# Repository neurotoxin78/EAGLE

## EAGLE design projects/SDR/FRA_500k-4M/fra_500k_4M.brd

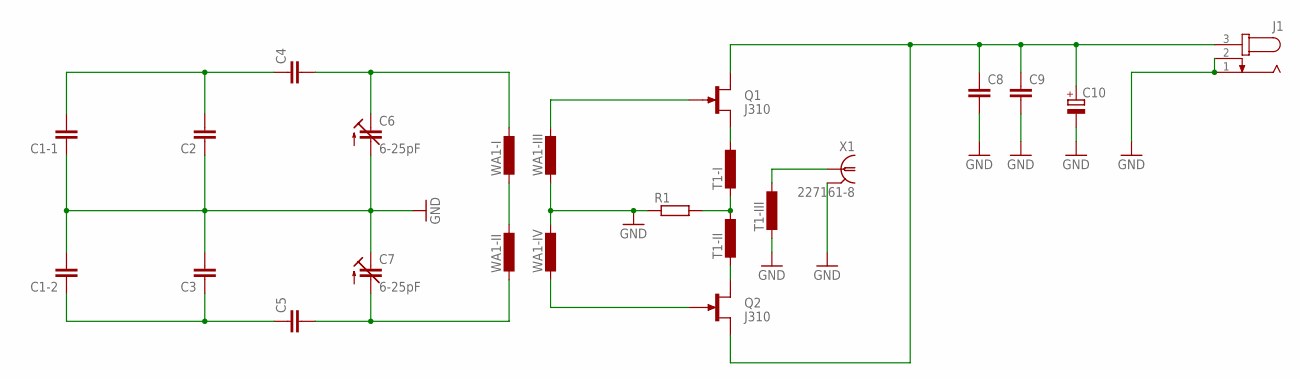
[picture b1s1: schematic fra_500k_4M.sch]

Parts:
C1-1, C1-2: C-EU075-032X103; C075-032X103
C2, C3, C4, C5: C-EUC1210; C1210
C6, C7: 6-25pF; CTRIM3050.504
C8, C9: C-EUC1206; C1206
C10: CPOL-EUSMCC; SMC_C
J1: JACK-PLUG0; SPC4077
Q1, Q2: J310; TO92R
R1: R-EU_M1206; M1206
T1-I, T1-II, T1-III: L-EU0204/7; 0204/7
WA1-I, WA1-II, WA1-III, WA1-IV: L-EU0204/7; 0204/7
X1: 227161-8; AMP_227161

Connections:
GND: C1-1.1, C1-2.2, C2.1, C3.2, C6.2 (A), C7.1 (E), C8.2, C9.2, C10.-, J1.1, J1.2, R1.1, T1-III.2, WA1-III.2, WA1-IV.1, X1.2
unnamed: Q1.G, WA1-III.1
unnamed: Q2.G, WA1-IV.2
unnamed: T1-III.1, X1.1
unnamed: Q1.S, T1-I.1
unnamed: R1.2, T1-I.2, T1-II.1
unnamed: Q2.D, T1-II.2
unnamed: C8.1, C9.1, C10.+, J1.3, Q1.D, Q2.S
unnamed: C4.2, C6.1 (E), WA1-I.1
unnamed: C1-1.2, C2.2, C4.1
unnamed: C1-2.1, C3.1, C5.1
unnamed: C5.2, C7.2 (A), WA1-II.2
unnamed: WA1-I.2, WA1-II.1

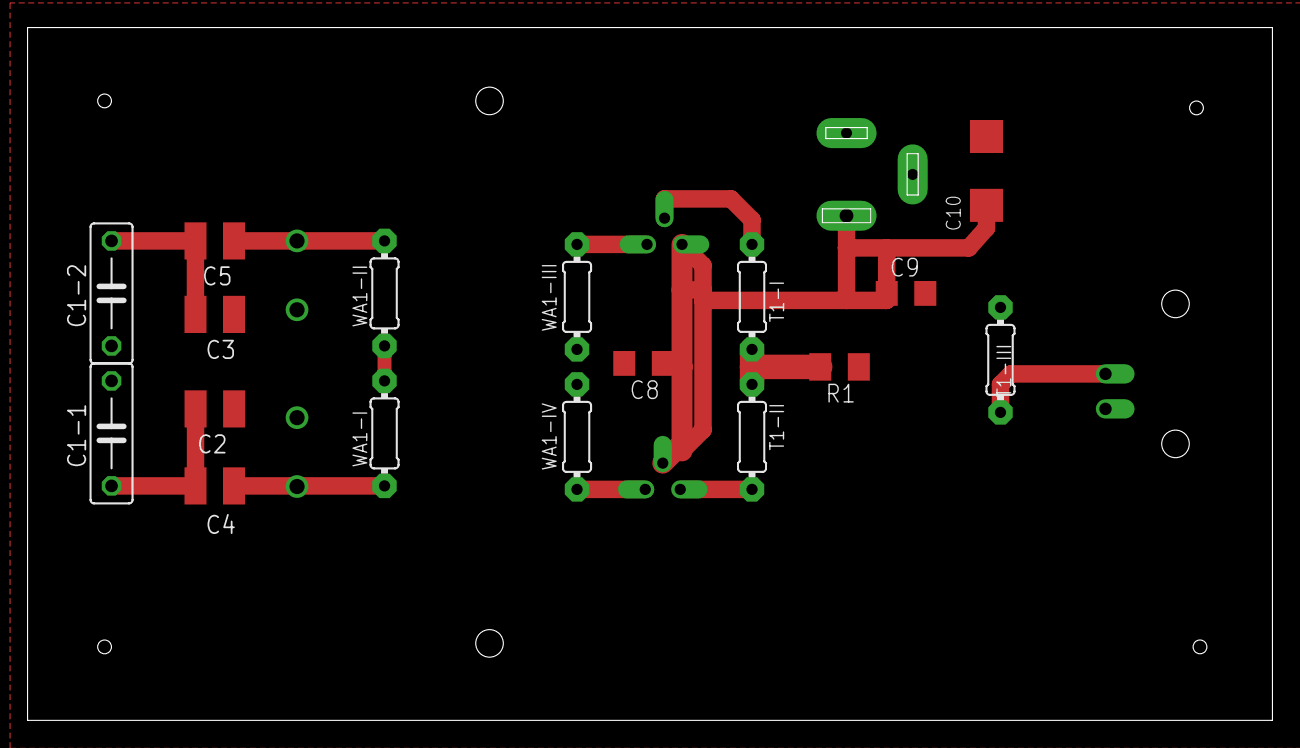
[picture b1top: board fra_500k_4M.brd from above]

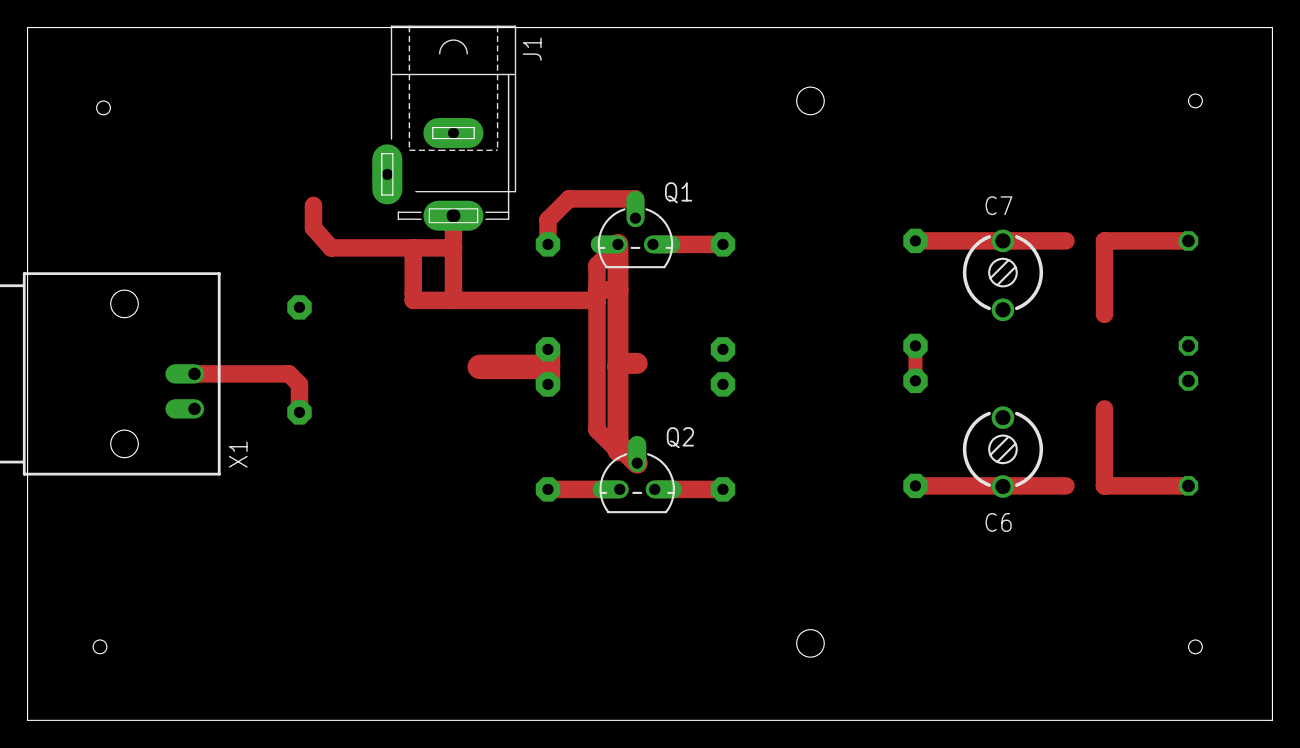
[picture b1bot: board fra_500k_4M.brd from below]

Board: 2 copper layers, 90.3 x 50.3 mm, 23 parts (6 on the bottom side), 13 nets.

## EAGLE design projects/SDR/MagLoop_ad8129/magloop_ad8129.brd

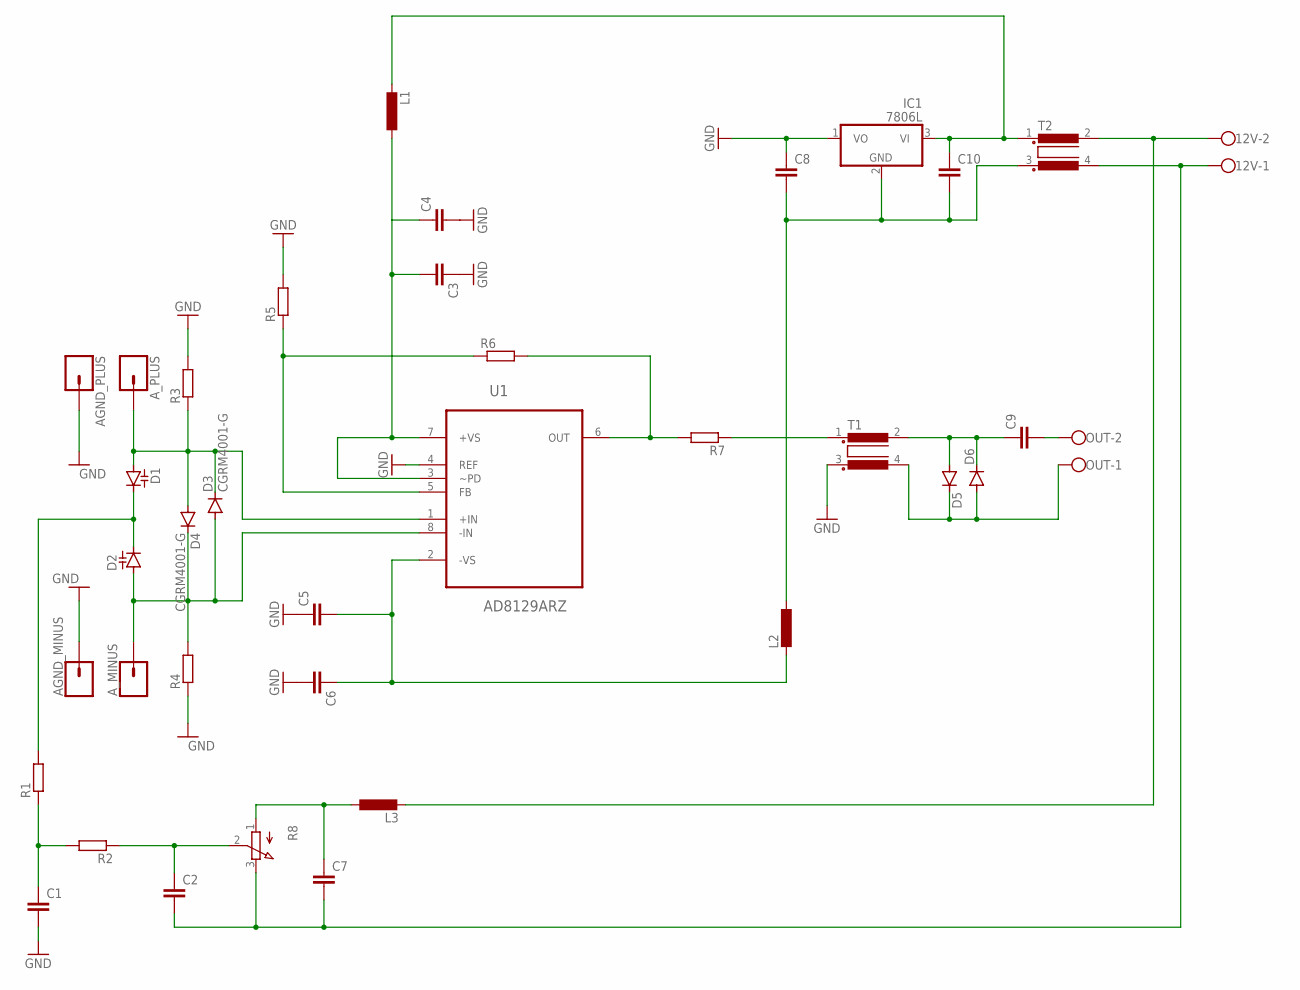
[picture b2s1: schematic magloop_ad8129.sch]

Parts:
12V: W237-102
AGND_MINUS: CONN_01PTH_2MM; 1X01_2MM
AGND_PLUS: CONN_01PTH_2MM; 1X01_2MM
A_MINUS: CONN_01PTH_2MM; 1X01_2MM
A_PLUS: CONN_01PTH_2MM; 1X01_2MM
C1, C2, C7: C-EUC0805K; C0805K
C3, C4, C5, C6, C8, C10: C-EUC1206K; C1206K
C9: C-EUC1206; C1206
D1, D2: DIODE_CAPACITANCE-SOT54H; SOT54H
D3, D4, D5, D6: CGRM4001-G; SOD-123_MINI-SMA
IC1: 7806L; TO92
L1, L2, L3: L-EU0207/10; 0207/10
OUT: W237-102
R1, R2, R5, R6: R-EU_R0805; R0805
R3, R4, R7: R-EU_R1206; R1206
R8: 3RP/1610N
T1, T2: R1405UB1/2; B1/2
U1: AD8129ARZ; SOIC127P600X175-8N

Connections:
GND: AGND_MINUS.1, AGND_PLUS.1, C1.2, C3.1, C4.2, C5.1, C6.2, C8.1, IC1.1 (VO), R3.2, R4.1, R5.2, T1.3, U1.4 (REF)
unnamed: A_PLUS.1, D1.A, D3.C, D4.A, R3.1, U1.1 (+IN)
unnamed: D1.C, D2.C, R1.2
unnamed: A_MINUS.1, D2.A, D3.A, D4.C, R4.2, U1.8 (-IN)
unnamed: R5.1, R6.1, U1.5 (FB)
unnamed: R6.2, R7.2, U1.6 (OUT)
unnamed: C1.1, R1.1, R2.2
unnamed: C2.1, R2.1, R8.2 (S)
unnamed: C7.1, L3.1, R8.1 (A)
unnamed: C3.2, C4.1, L1.1, U1.3 (~PD), U1.7 (+VS)
unnamed: C10.1, IC1.3 (VI), L1.2, T2.1
unnamed: C8.2, C10.2, IC1.2 (GND), L2.1, T2.3
unnamed: 12V.2, L3.2, T2.2
unnamed: 12V.1, C2.2, C7.2, R8.3 (E), T2.4
unnamed: C5.2, C6.1, L2.2, U1.2 (-VS)
unnamed: R7.1, T1.1
unnamed: C9.1, D5.A, D6.C, T1.2
unnamed: C9.2, OUT.2
unnamed: D5.C, D6.A, OUT.1, T1.4

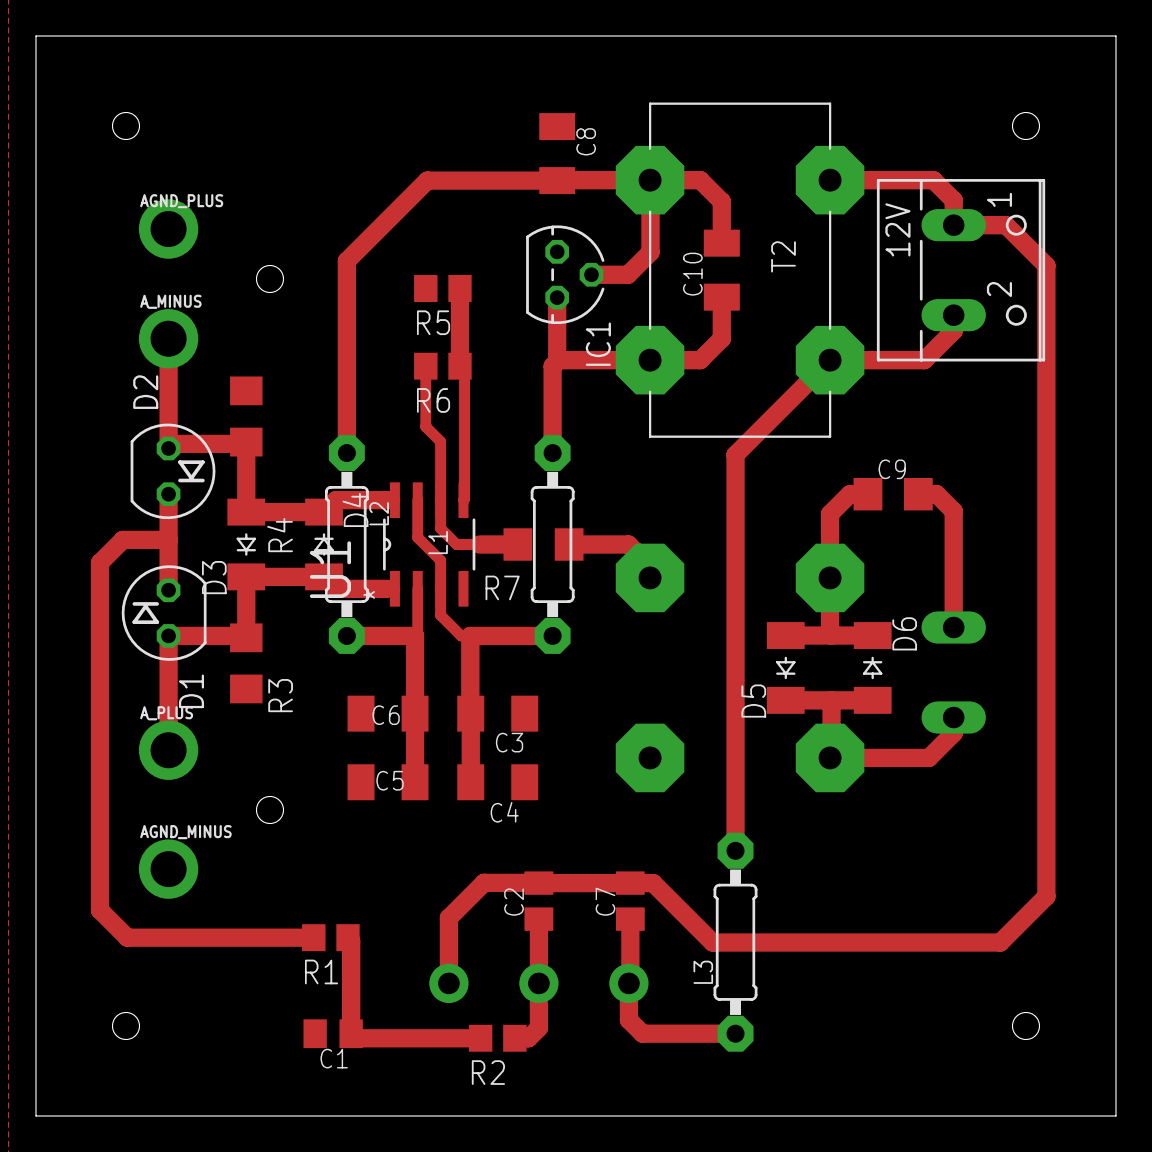
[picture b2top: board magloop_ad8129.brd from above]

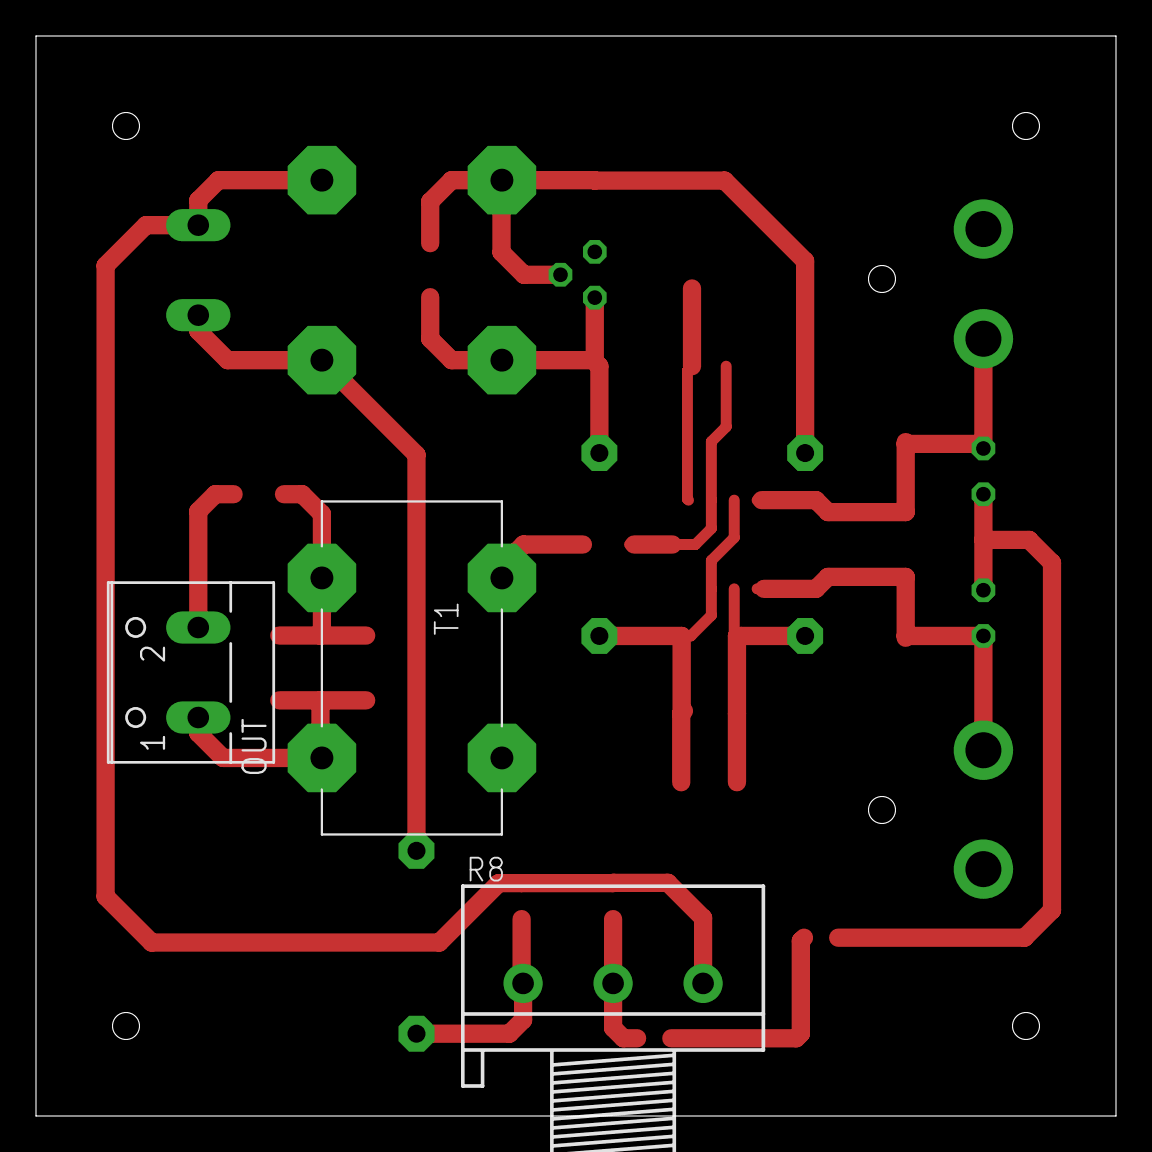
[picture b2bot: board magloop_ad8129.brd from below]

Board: 2 copper layers, 60.0 x 60.0 mm, 37 parts (3 on the bottom side), 19 nets.

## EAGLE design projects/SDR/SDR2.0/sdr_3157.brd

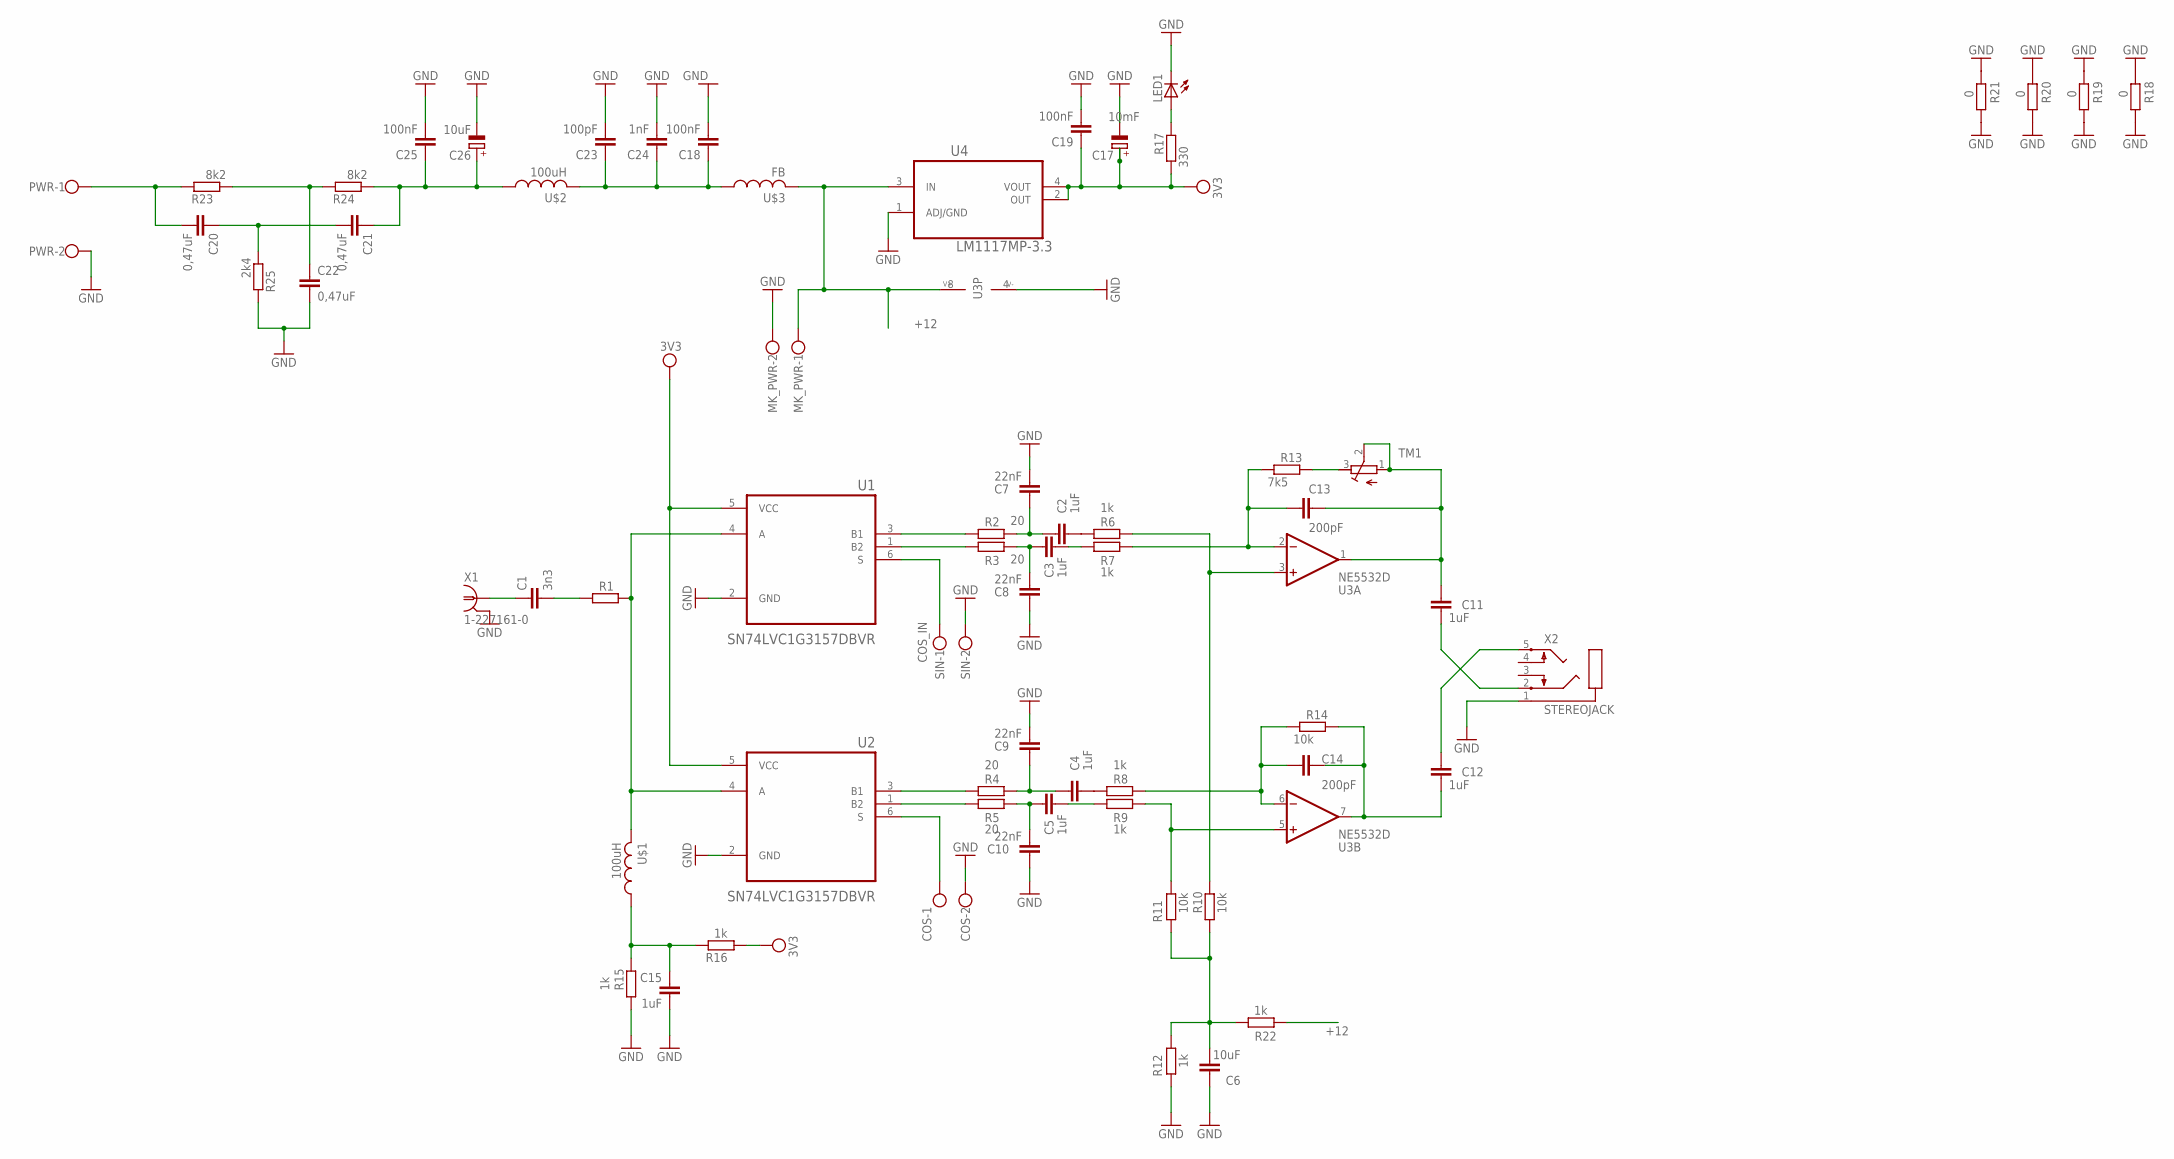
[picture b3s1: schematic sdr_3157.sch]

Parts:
C1: 3n3; C0805
C2, C3, C4, C5, C15: 1uF; C0805
C6: 10uF; C0805
C7, C8, C9, C10: 22nF; C0805
C11, C12: 1uF; C1210K
C13, C14: 200pF; C0805
C17: 10mF; SMC_C
C18, C19, C25: 100nF; C0805
C20, C21, C22: 0,47uF; C0805
C23: 100pF; C0805
C24: 1nF; C0805
C26: 10uF; SMC_C
COS: W237-102
LED1: LEDSMT1206; 1206
MK_PWR: W237-102
PWR: W237-102
R1: R-EU_R0805; R0805
R2, R3, R4, R5: 20; R0805
R6, R7, R9, R15, R16: 1k; R0805
R8: 1k; 0204/7
R10, R14: 10k; R0805
R11: 10k; 0207/12
R12, R22: 1k; M0805
R13: 7k5; R0805
R17: 330; R0805
R18, R21: 0; 0207/12
R19: 0; 0207/5V
R20: 0; 0204/7
R23, R24: 8k2; R0805
R25: 2k4; R0805
SIN: W237-102
TM1: 5k; RTRIM3296W
U1, U2: SN74LVC1G3157DBVR; SOT95P280X145-6N
U3: NE5532D; SO08
U4: LM1117MP-3.3; SOT230P696X180-4N
U$1, U$2: 100uH; LQH55
U$3: FB
X1: 1-227161-0; AMP_227161
X2: STEREOJACK; STX3100

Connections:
+12: MK_PWR.1, R22.1, U3.8 (V+), U4.3 (IN), U$3.P$2 (2)
COS_IN: SIN.1, U1.6 (S)
GND: C6.1, C7.2, C8.1, C9.2, C10.1, C15.1, C17.-, C18.2, C19.2, C22.2, C23.2, C24.2, C25.2, C26.-, COS.2, LED1.C, MK_PWR.2, PWR.2, R12.1, R15.1, R18.1, R18.2, R19.1, R19.2, R20.1, R20.2, R21.1, R21.2, R25.2, SIN.2, U1.2 (GND), U2.2 (GND), U3.4 (V-), U4.1 (ADJ/GND), X1.2, X2.1
unnamed: R1.2, U1.4 (A), U2.4 (A), U$1.2
unnamed: C1.2, R1.1
unnamed: R2.1, U1.3 (B1)
unnamed: R3.1, U1.1 (B2)
unnamed: R4.1, U2.3 (B1)
unnamed: C1.1, X1.1
unnamed: R5.1, U2.1 (B2)
unnamed: C2.1, C7.1, R2.2
unnamed: C3.1, C8.2, R3.2
unnamed: C4.1, C9.1, R4.2
unnamed: C5.1, C10.2, R5.2
unnamed: C2.2, R6.1
unnamed: C3.2, R7.1
unnamed: C4.2, R8.1
unnamed: C5.2, R9.1
unnamed: R6.2, R10.2, U3.3 (+IN)
unnamed: C13.1, R7.2, R13.1, U3.2 (-IN)
unnamed: R9.2, R11.2, U3.5 (+IN)
unnamed: C14.1, R8.2, R14.1, U3.6 (-IN)
unnamed: C6.2, R10.1, R11.1, R12.2, R22.2
unnamed: C11.1, C13.2, TM1.1 (A), TM1.2 (S), U3.1 (OUT)
unnamed: C11.2, X2.2
unnamed: C12.1, X2.5
unnamed: C12.2, C14.2, R14.2, U3.7 (OUT)
unnamed: C15.2, R15.2, R16.2, U$1.1
unnamed: LED1.A, R17.2
unnamed: C20.2, PWR.1, R23.2
unnamed: R13.2, TM1.3 (E)
unnamed: C22.1, R23.1, R24.2
unnamed: C20.1, C21.2, R25.1
unnamed: COS.1, U2.6 (S)
unnamed: C21.1, C25.1, C26.+, R24.1, U$2.1
unnamed: C18.1, C23.1, C24.1, U$2.2, U$3.P$1 (1)
VCC: C17.+, C19.1, R16.1, R17.1, U1.5 (VCC), U2.5 (VCC), U4.2 (OUT), U4.4 (VOUT)

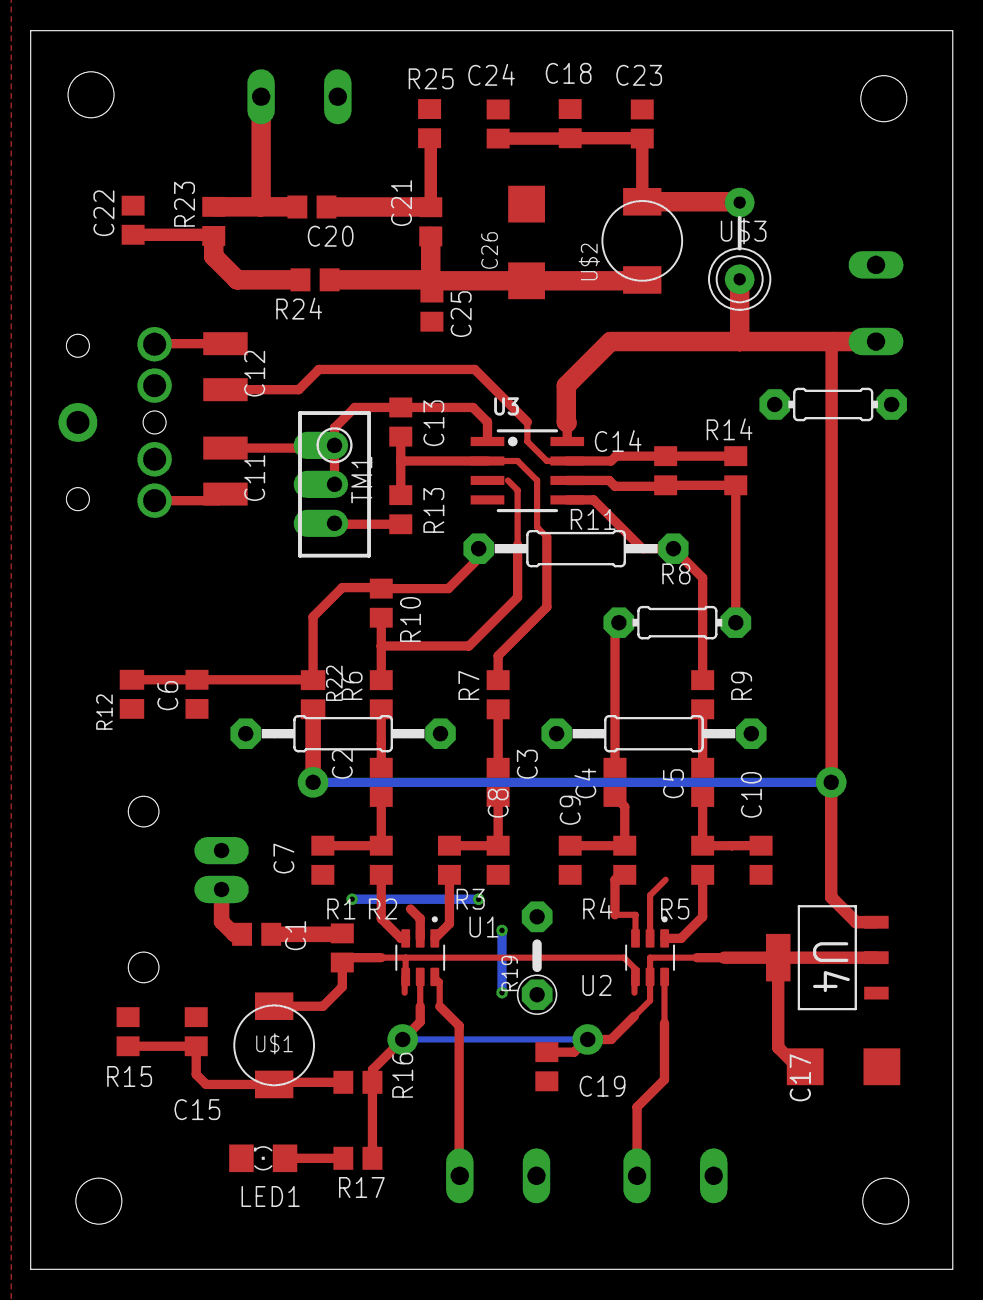
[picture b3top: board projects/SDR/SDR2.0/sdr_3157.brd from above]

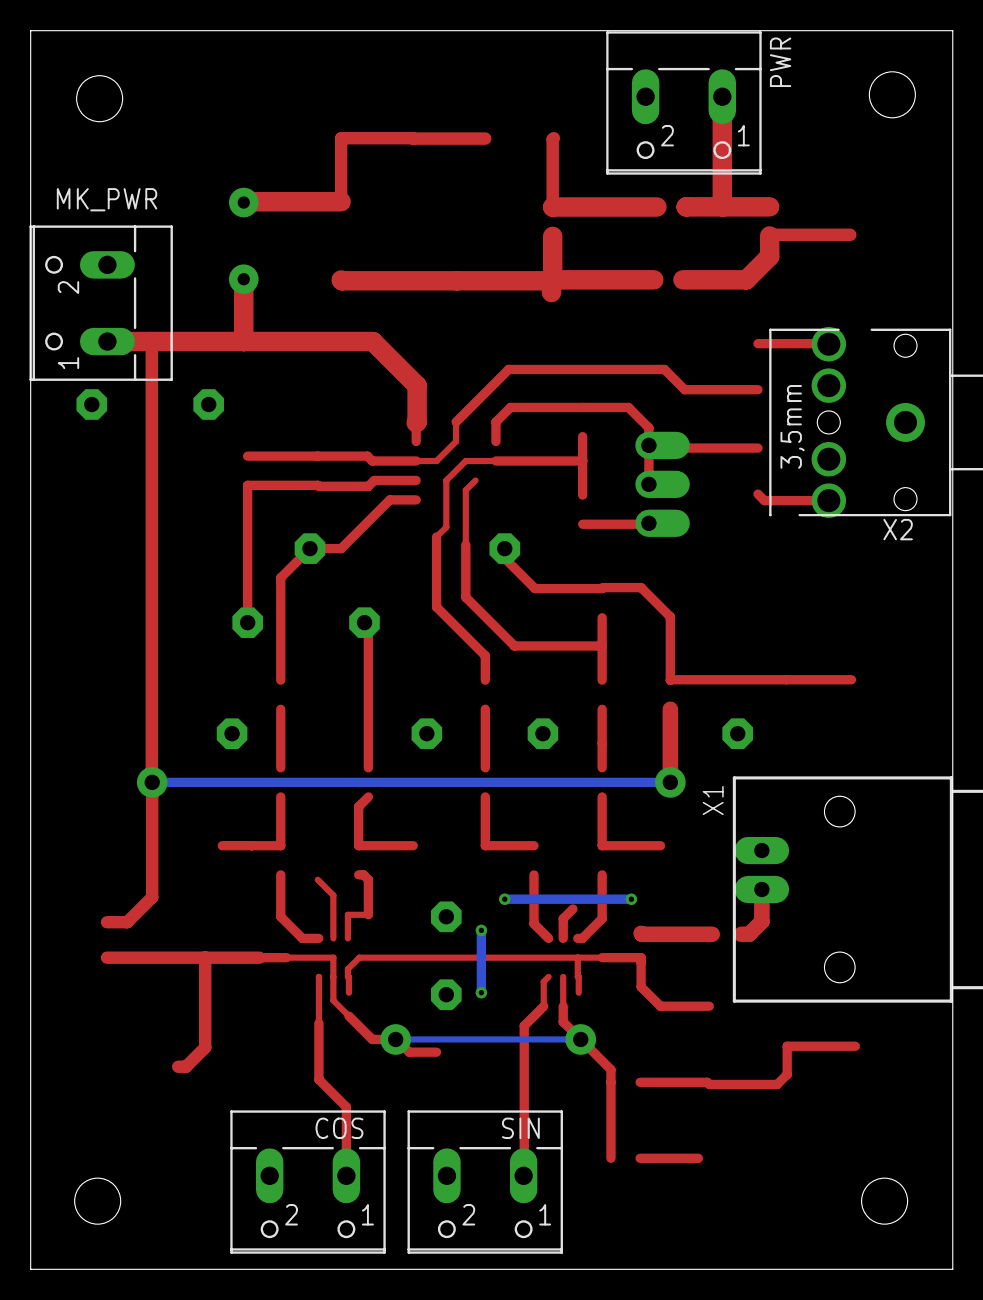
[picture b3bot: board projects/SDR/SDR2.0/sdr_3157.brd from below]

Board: 2 copper layers, 60.1 x 80.8 mm, 65 parts (6 on the bottom side), 37 nets.

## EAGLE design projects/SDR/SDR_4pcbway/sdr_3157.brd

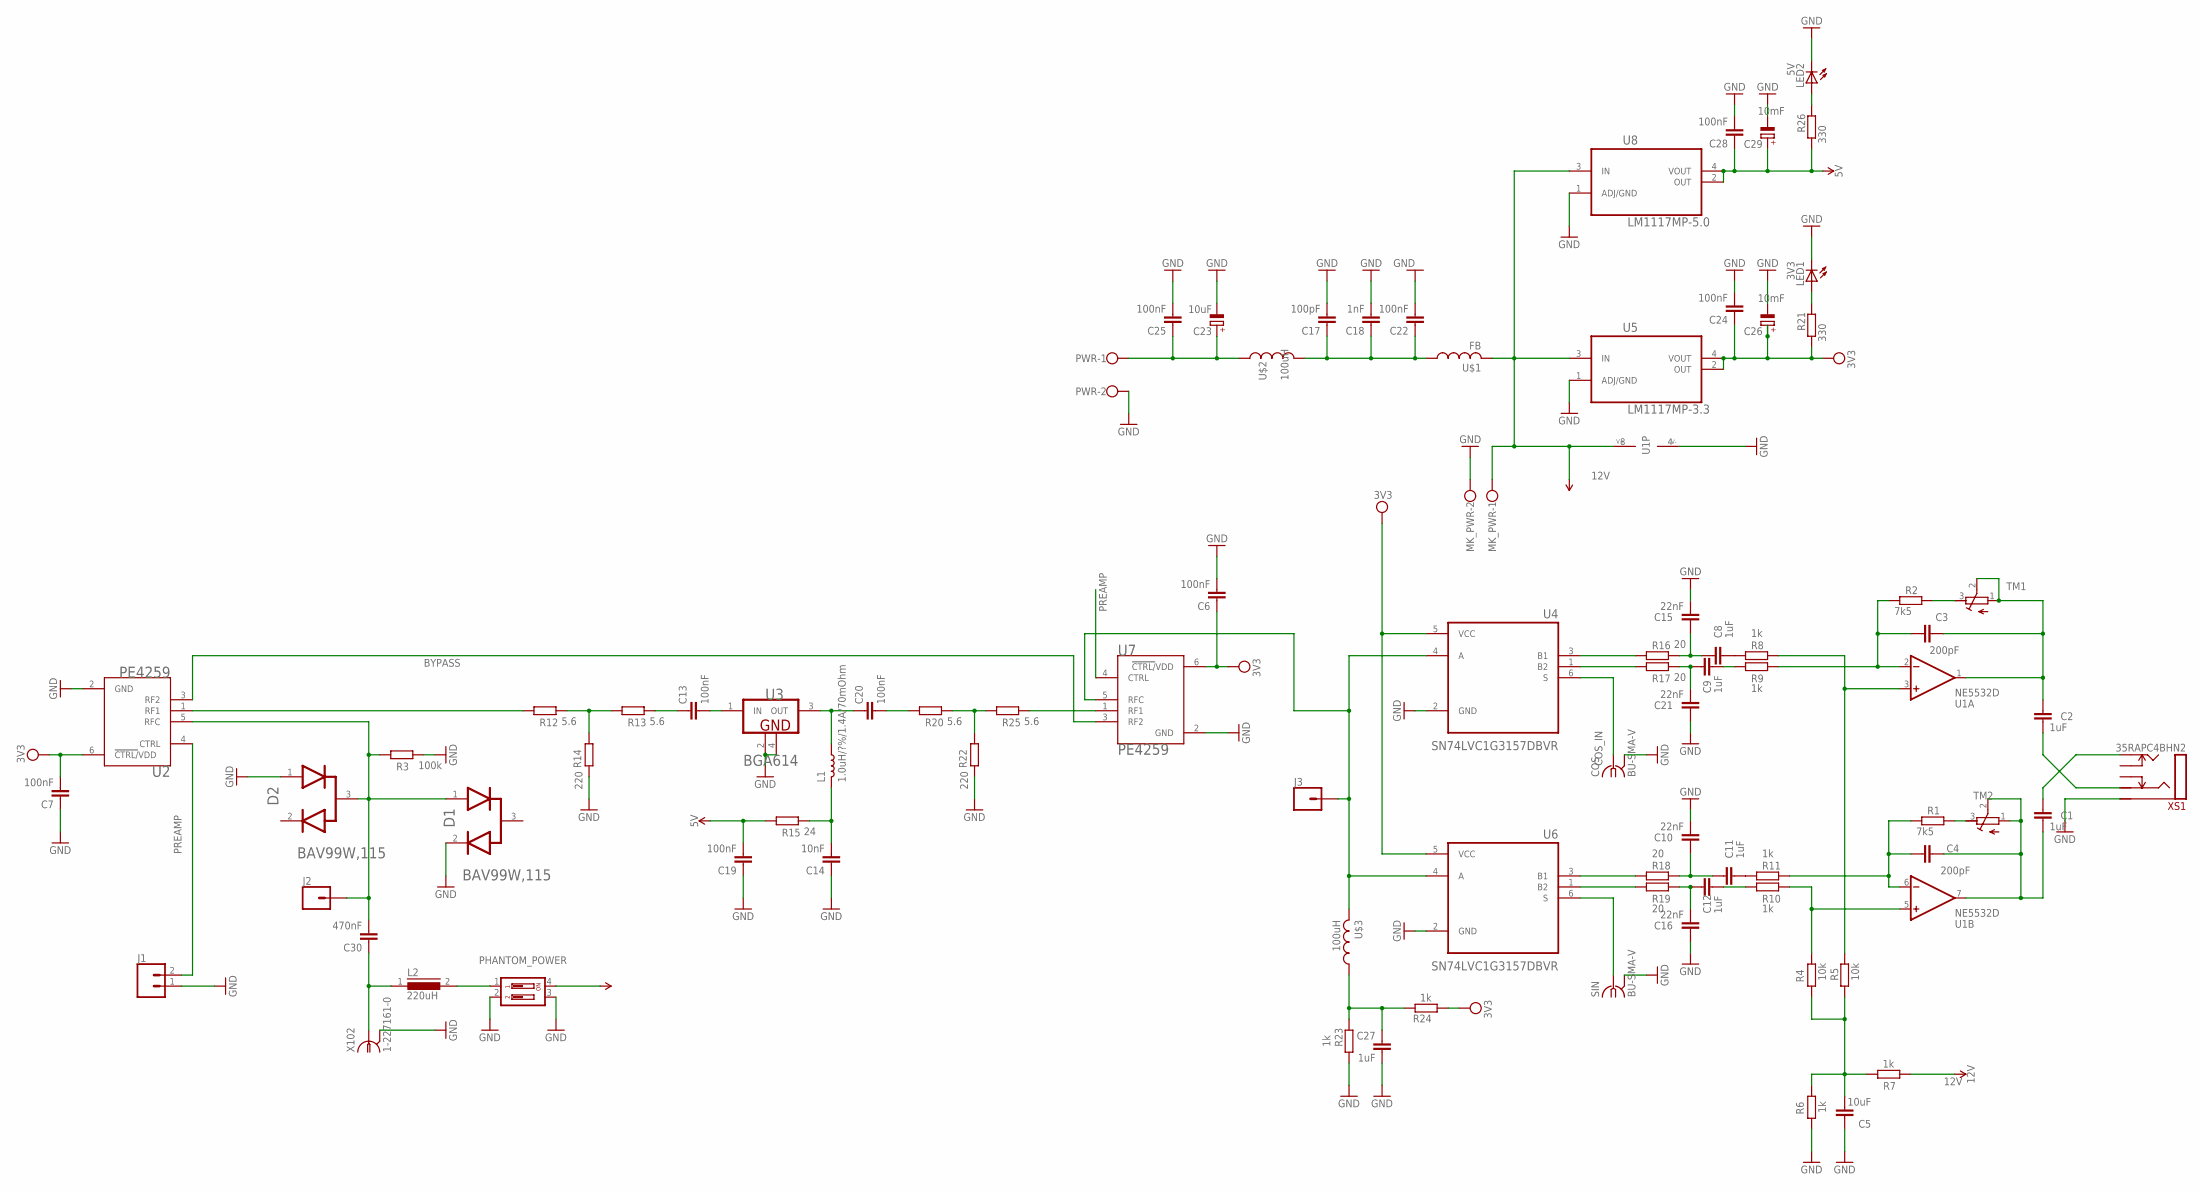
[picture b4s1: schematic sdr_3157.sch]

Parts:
C1, C2: 1uF; C050-045X075
C3, C4: 200pF; C050-045X075
C5: 10uF; C0805
C6, C7, C13, C19, C20, C22, C24, C25, C28: 100nF; C0805
C8, C9, C11, C12, C27: 1uF; C0805
C10, C15, C16, C21: 22nF; C0805
C14: 10nF; C0805
C17: 100pF; C0805
C18: 1nF; C0805
C23: 10uF; SMC_C
C26, C29: 10mF; SMC_C
C30: 470nF; C0805
COS: BU-SMA-V
D1, D2: NEXPERIA_BAV99W,115NEXPERIA_BAV99W,115_0_0; NEXPERIA_BAV99W,115_0
J1: CONN_02; 1X02
J2, J3: CONN_01PTH_NO_SILK_SMALL; 1X01_SMALL
L1: 1.0uH/?%/1.4A/70mOhm; 0805-WIDE
L2: 220uH; DR73
LED1: 3V3; 1206
LED2: 5V; 1206
MK_PWR: W237-102
PHANTOM_POWER: DIP02YL
PWR: W237-102
R1, R2: 7k5; R0805
R3: 100k; R0805
R4: 10k; M0805
R5: 10k; R0805
R6, R7, R11: 1k; M0805
R8, R9, R10, R23, R24: 1k; R0805
R12, R13, R20, R25: 5.6; R0805
R14, R22: 220; R0805
R15: 24; R0805
R16, R17, R18, R19: 20; R0805
R21, R26: 330; R0805
SIN: BU-SMA-V
TM1, TM2: 5k; RTRIM3296W
U1: NE5532D; SO08
U2, U7: PE4259; SOT65P215X110-6N
U3: INFINEON_BGA614INFINEON_BGA614_0_0; INFINEON_BGA614_0
U4, U6: SN74LVC1G3157DBVR; SOT95P280X145-6N
U5: LM1117MP-3.3; SOT230P696X180-4N
U8: LM1117MP-5.0; SOT230P696X180-4N
U$1: FB
U$2: 100uH; IHLP4040
U$3: 100uH; LQH55
X102: 1-227161-0; AMP_227161
XS1: 35RAPC4BHN2; 35RAP

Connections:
5V: C19.2, C28.1, C29.+, R15.1, R26.1, U8.2 (OUT), U8.4 (VOUT)
12V: MK_PWR.1, PHANTOM_POWER.4, R7.1, U1.8 (V+), U5.3 (IN), U8.3 (IN), U$1.P$2 (2)
BYPASS: U2.3 (RF2), U7.3 (RF2)
COS_IN: COS.1, U4.6 (S)
GND: C5.1, C6.2, C7.1, C10.2, C14.1, C15.2, C16.1, C17.2, C18.2, C19.1, C21.1, C22.2, C23.-, C24.2, C25.2, C26.-, C27.1, C28.2, C29.-, COS.2, COS.3 (2), COS.4 (2), COS.5 (2), D1.2 (2_CATHODE), D2.1 (1_ANODE), J1.1, LED1.C, LED2.C, MK_PWR.2, PHANTOM_POWER.2, PHANTOM_POWER.3, PWR.2, R3.2, R6.1, R14.2, R22.2, R23.1, SIN.2, SIN.3 (2), SIN.4 (2), SIN.5 (2), U1.4 (V-), U2.2 (GND), U3.2 (1_GND), U3.4 (2_GND), U4.2 (GND), U5.1 (ADJ/GND), U6.2 (GND), U7.2 (GND), U8.1 (ADJ/GND), X102.2, XS1.1 (S)
unnamed: J3.P$1, U4.4 (A), U6.4 (A), U7.5 (RFC), U$3.2
unnamed: R25.2, U7.1 (RF1)
unnamed: R16.1, U4.3 (B1)
unnamed: R17.1, U4.1 (B2)
unnamed: R18.1, U6.3 (B1)
unnamed: R12.1, U2.1 (RF1)
unnamed: R19.1, U6.1 (B2)
unnamed: C8.1, C15.1, R16.2
unnamed: C9.1, C21.2, R17.2
unnamed: C10.1, C11.1, R18.2
unnamed: C12.1, C16.2, R19.2
unnamed: C8.2, R8.1
unnamed: C9.2, R9.1
unnamed: C11.2, R11.1
unnamed: C12.2, R10.1
unnamed: R5.2, R8.2, U1.3 (+IN)
unnamed: C3.1, R2.1, R9.2, U1.2 (-IN)
unnamed: R4.2, R10.2, U1.5 (+IN)
unnamed: C4.1, R1.1, R11.2, U1.6 (-IN)
unnamed: C5.2, R4.1, R5.1, R6.2, R7.2
unnamed: C2.1, C3.2, TM1.1 (A), TM1.2 (S), U1.1 (OUT)
unnamed: C2.2, XS1.3 (R)
unnamed: C1.1, XS1.2 (T)
unnamed: C1.2, C4.2, TM2.1 (A), TM2.2 (S), U1.7 (OUT)
unnamed: C27.2, R23.2, R24.2, U$3.1
unnamed: LED1.A, R21.2
unnamed: R12.2, R13.1, R14.1
unnamed: R2.2, TM1.3 (E)
unnamed: C13.2, U3.1 (IN)
unnamed: C13.1, R13.2
unnamed: SIN.1, U6.6 (S)
unnamed: C23.+, C25.1, PWR.1, U$2.1
unnamed: C17.1, C18.1, C22.1, U$1.P$1 (1), U$2.2
unnamed: C20.1, L1.1, U3.3 (OUT)
unnamed: C20.2, R20.1
unnamed: R20.2, R22.1, R25.1
unnamed: C30.1, L2.1, X102.1
unnamed: C14.2, L1.2, R15.2
unnamed: C30.2, D1.1 (1_ANODE), D2.3 (1_CATHODE/2_ANODE), J2.P$1, R3.1, U2.5 (RFC)
unnamed: LED2.A, R26.2
unnamed: R1.2, TM2.3 (E)
unnamed: L2.2, PHANTOM_POWER.1
PREAMP: J1.2, U2.4 (CTRL), U7.4 (CTRL)
VCC: C6.1, C7.2, C24.1, C26.+, R21.1, R24.1, U2.6 (!CTRL/!VDD), U4.5 (VCC), U5.2 (OUT), U5.4 (VOUT), U6.5 (VCC), U7.6 (!CTRL/!VDD)

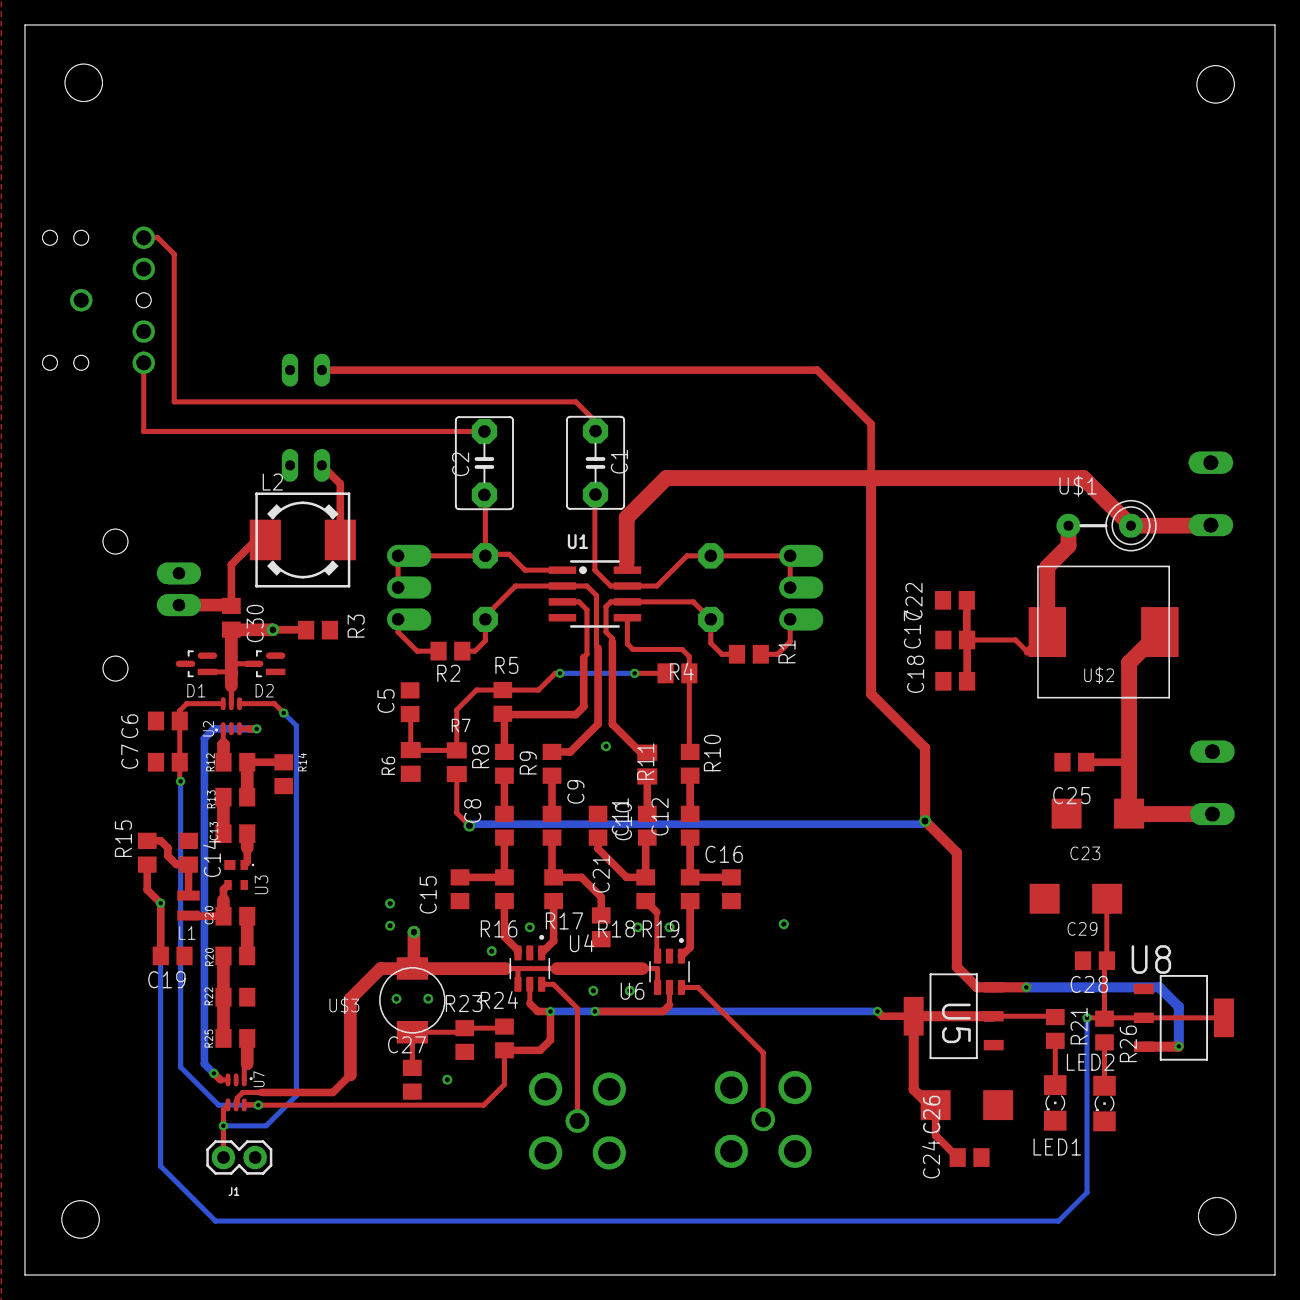
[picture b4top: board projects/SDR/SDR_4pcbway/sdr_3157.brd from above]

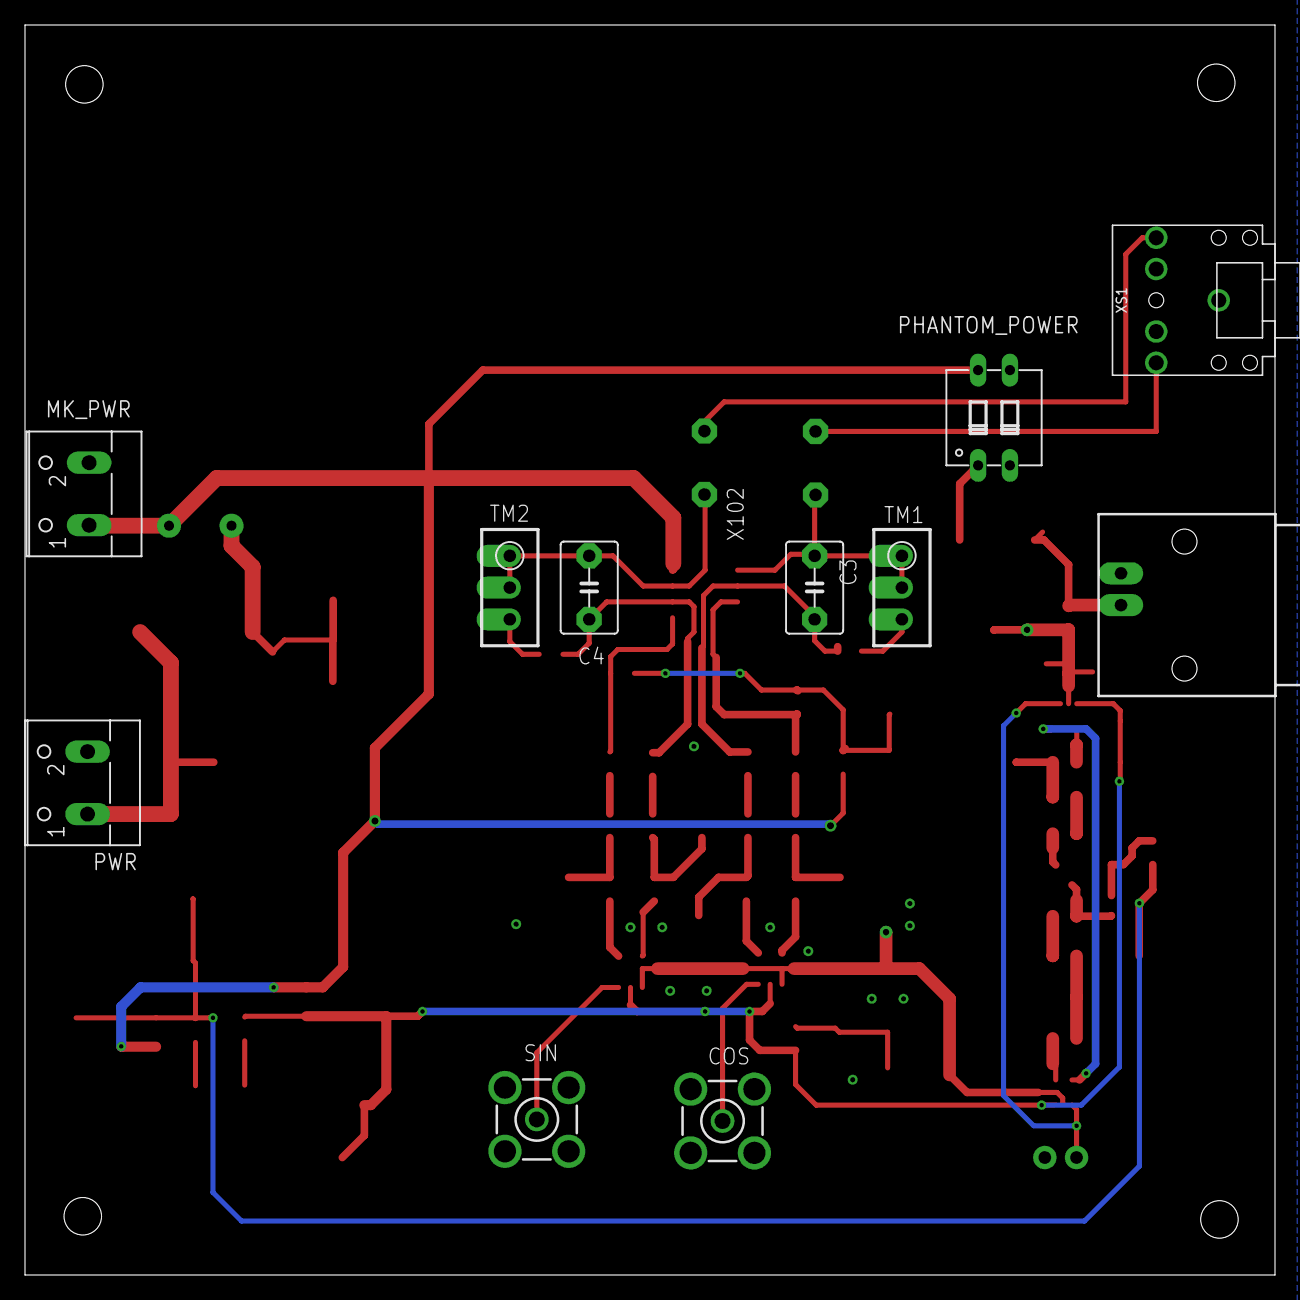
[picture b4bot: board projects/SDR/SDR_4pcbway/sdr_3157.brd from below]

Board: 2 copper layers, 100.0 x 100.0 mm, 85 parts (11 on the bottom side), 49 nets.

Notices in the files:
parts and their libraries:
SparkFun-Connectors: Licensing: Creative Commons ShareAlike 4.0 International - https://creativecommons.org/licenses/by-sa/4.0
op-amp: Copyright (C) 2006 by Bob Starr
